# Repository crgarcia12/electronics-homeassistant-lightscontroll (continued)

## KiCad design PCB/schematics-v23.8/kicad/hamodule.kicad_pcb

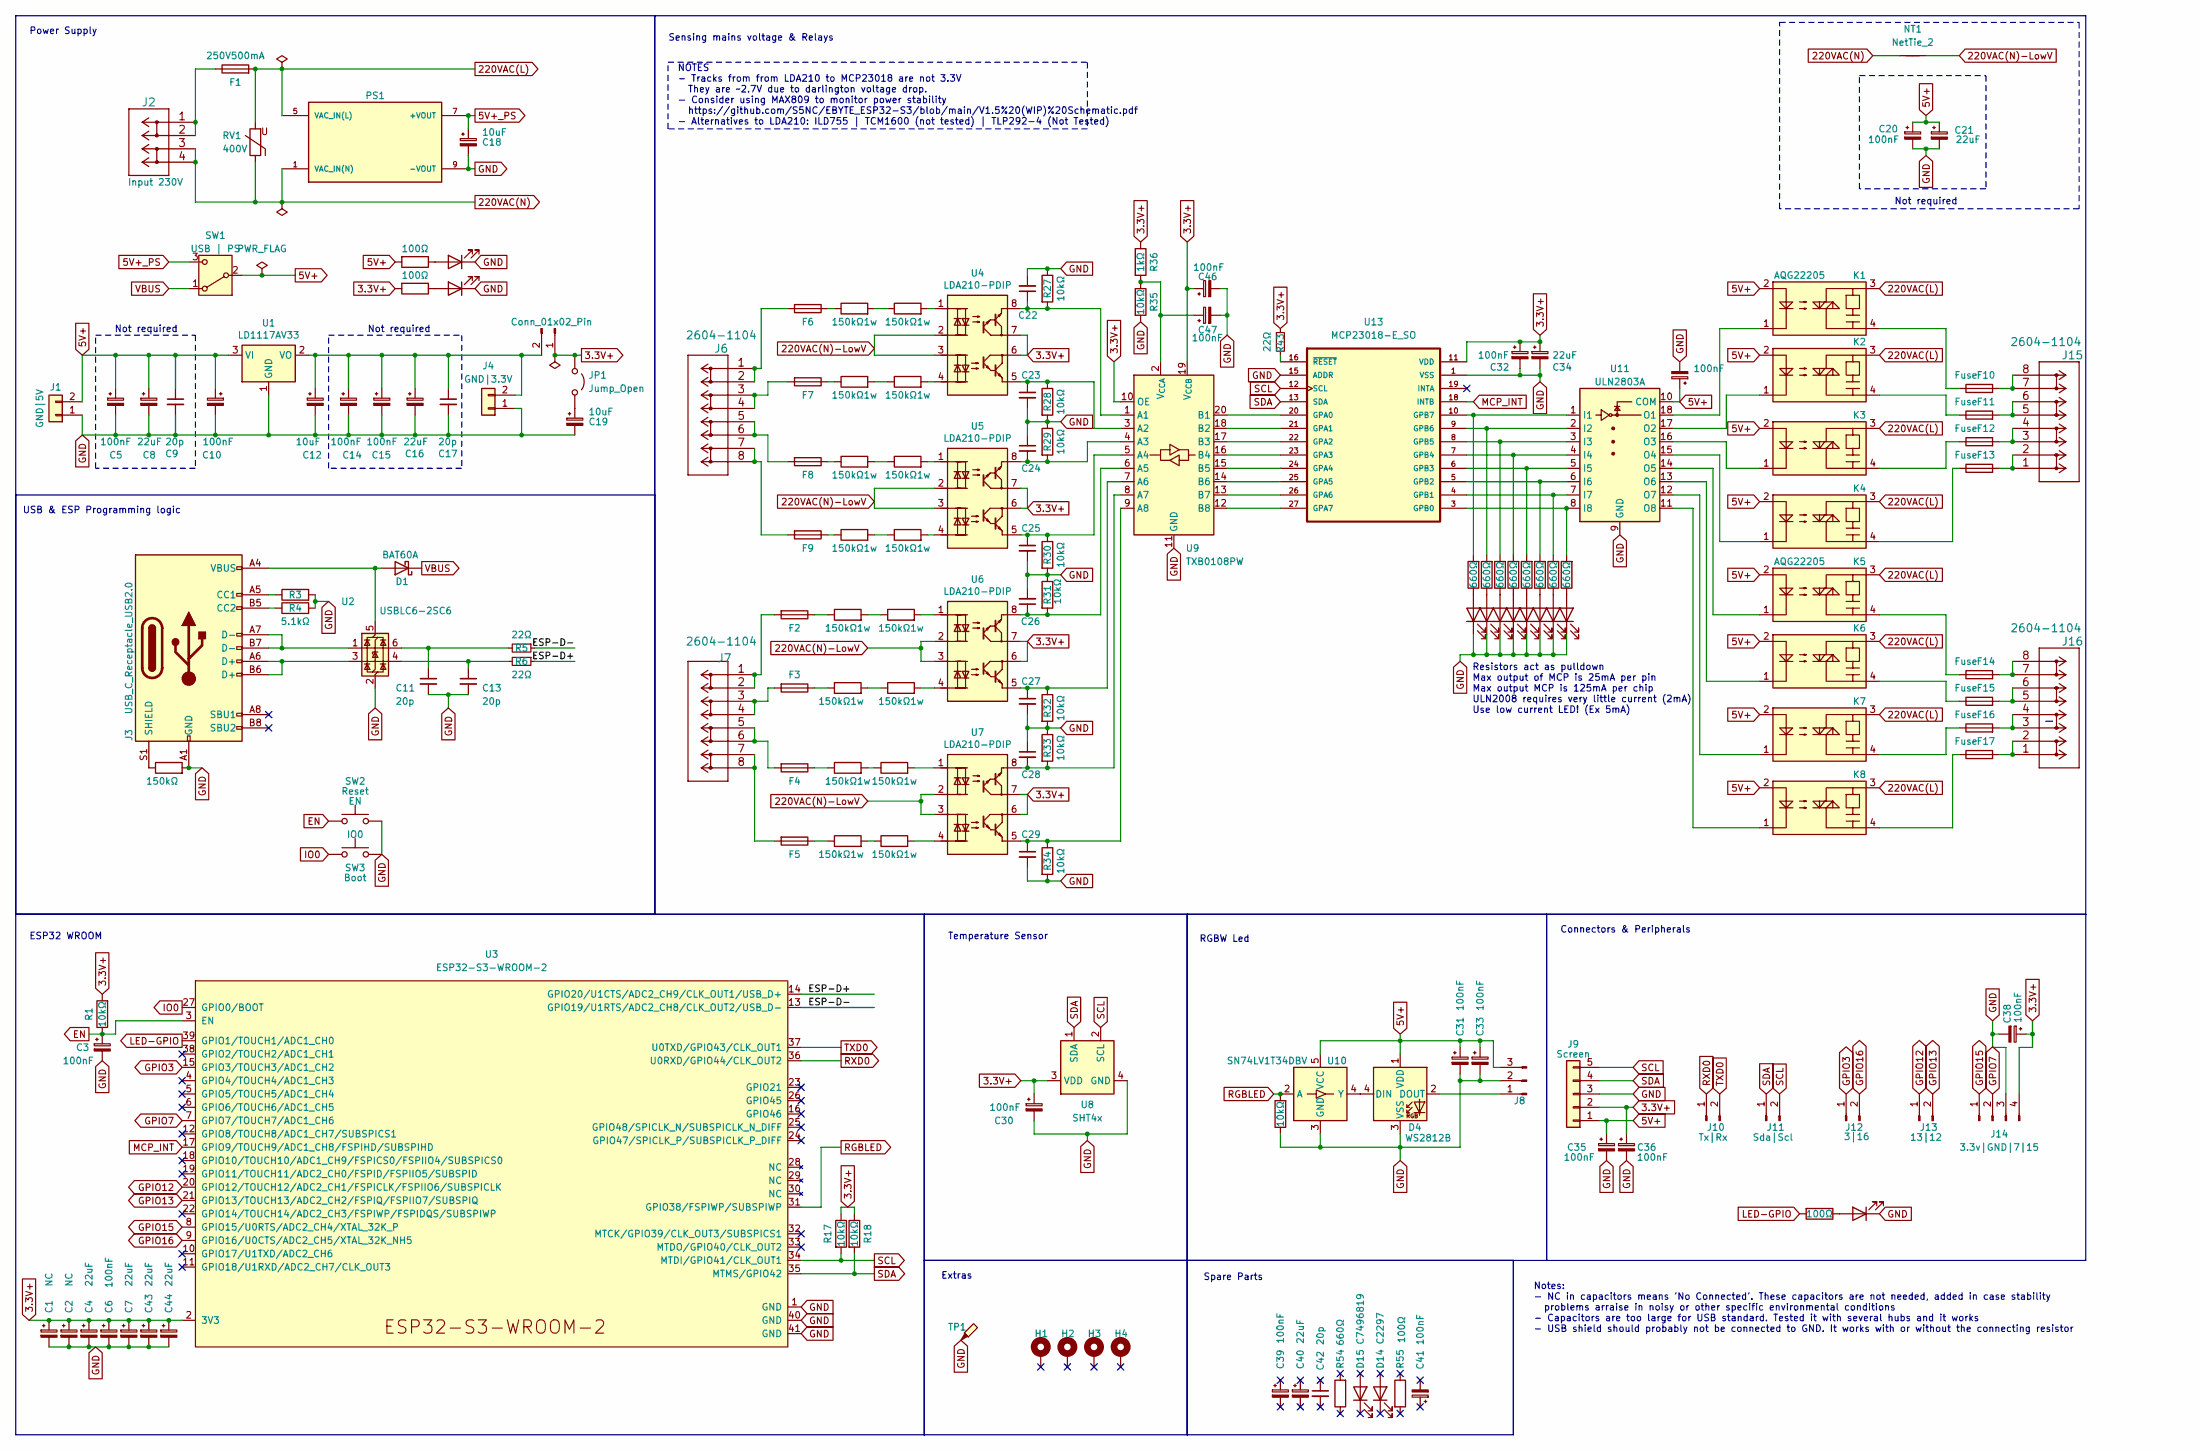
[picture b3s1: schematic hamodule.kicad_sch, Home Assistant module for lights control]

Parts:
C1, C2: NC; C_1206_3216Metric_Pad1.33x1.80mm_HandSolder
C3, C6, C30, C31, C33, C39, C46, C47: 100nF; C_0603_1608Metric_Pad1.08x0.95mm_HandSolder; JLCPCB C14663
C4, C22, C23, C24, C25, C26, C27, C28, C29, C34, C40: 22uF; C_0603_1608Metric_Pad1.08x0.95mm_HandSolder; JLCPCB C59461
C5, C10, C14, C15, C20, C32, C35, C36, C37, C38, C41: 100nF; C_0805_2012Metric_Pad1.18x1.45mm_HandSolder; JLCPCB C49678
C7, C8, C16, C21: 22uF; C_0805_2012Metric_Pad1.18x1.45mm_HandSolder; JLCPCB C45783
C9, C11, C13, C17, C42: 20p; C_0603_1608Metric_Pad1.08x0.95mm_HandSolder; LCSC C1648
C12, C18, C19: 10uF; CP_Radial_D6.3mm_P2.50mm
C43, C44: 22uF; C_0402_1005Metric; LCSC \
D1: BAT60A; D_SOD-323; JLCPCB C124187
D2: 5V; LED_0805_2012Metric_Pad1.15x1.40mm_HandSolder; JLCPCB C2297
D3: 3.3V; LED_0805_2012Metric_Pad1.15x1.40mm_HandSolder; JLCPCB C2297
D4: WS2812B; LED_WS2812B_PLCC4_5.0x5.0mm_P3.2mm; JLCPCB C5446705
D5, D6, D7, D8, D9, D10, D11, D12: LED; LED_0603_1608Metric; JLCPCB C7496819
D13: LED; LED_0805_2012Metric_Pad1.15x1.40mm_HandSolder; JLCPCB C2297
D14: C2297; LED_0805_2012Metric_Pad1.15x1.40mm_HandSolder; JLCPCB C2297
D15: C7496819; LED_0603_1608Metric; JLCPCB C7496819
F1: 250V500mA; Fuseholder_TR5_Littelfuse_No560_No460
F2, F3, F4, F5, F6, F7, F8, F9, F10, F11, F12, F13, F14, F15, F16, F17: Fuse; FUSE_RST-1-BULK
H1, H2, H3, H4: MountingHole_Pad; MountingHole_3.2mm_M3_ISO14580_Pad
J1: GND|5V; JST_XH_B2B-XH-A_1x02_P2.50mm_Vertical
J2: 2604-1102; big_pads_2604-1102
J3: USB_C_Receptacle_USB2.0; USB_C_Receptacle_HRO_TYPE-C-31-M-12; JLCPCB C2927038
J4: GND|3.3V; JST_XH_B2B-XH-A_1x02_P2.50mm_Vertical
J5: Conn_01x02_Pin; PinHeader_1x02_P2.54mm_Vertical; JLCPCB C492401
J6, J7, J15, J16: 2604-1104; big_pads_2604-1104
J8: 5v|GND|Do; PinHeader_1x03_P2.54mm_Vertical; JLCPCB C49257
J9: Screen; JST_XH_B5B-XH-A_1x05_P2.50mm_Vertical
J10: Tx|Rx; PinHeader_1x02_P2.54mm_Vertical; JLCPCB C492401
J11: Sda|Scl; PinHeader_1x02_P2.54mm_Vertical; JLCPCB C492401
J12: 3|16; PinHeader_1x02_P2.54mm_Vertical; JLCPCB C492401
J13: 13|12; PinHeader_1x02_P2.54mm_Vertical; JLCPCB C492401
J14: 3.3v|GND|7|15; PinHeader_1x04_P2.54mm_Vertical
JP1: Jump_Open; SolderJumper-2_P1.3mm_Bridged2Bar_RoundedPad1.0x1.5mm
K1, K2, K3, K4, K5, K6, K7, K8: AQG22205; AQG12205; Manufacturer_Part_Number AQG12205; Mouser Part Number 769-AQG12205
NT1: NetTie_2; NetTie-2_SMD_Pad2.0mm
PS1: RAC05-05SK/277; 277; PARTREV N/A
R1, R17, R18, R27, R28, R29, R30, R31, R32, R33, R34, R35, R44: 10kΩ; R_0603_1608Metric_Pad0.98x0.95mm_HandSolder; JLCPCB C25804
R2: 150kΩ; R_0805_2012Metric_Pad1.20x1.40mm_HandSolder; JLCPCB C17470
R3, R4: 5.1kΩ; R_0603_1608Metric_Pad0.98x0.95mm_HandSolder; JLCPCB C23186
R5, R6, R43: 22Ω; R_0603_1608Metric; LCSC C23345
R7, R8, R53, R55: 100Ω; R_0805_2012Metric_Pad1.20x1.40mm_HandSolder; JLCPCB C17408
R9, R10, R11, R12, R13, R14, R15, R16, R19, R20, R21, R22, R23, R24, R25, R26: 150kΩ1w; R_2512_6332Metric_Pad1.40x3.35mm_HandSolder; JLCPCB C25719
R36: 1kΩ; R_0603_1608Metric_Pad0.98x0.95mm_HandSolder
R45, R46, R47, R48, R49, R50, R51, R52, R54: 660Ω; R_0603_1608Metric_Pad0.98x0.95mm_HandSolder; JLCPCB C23193
RV1: 400V; RV_Disc_D12mm_W4.2mm_P7.5mm
SW1: USB | PS; PinHeader_1x03_P2.54mm_Vertical
SW2: Reset; SW_SPST_SKQG_WithStem; JLCPCB C318884
SW3: Boot; SW_SPST_SKQG_WithStem; JLCPCB C318884
TP1: GND; TestPoint_THTPad_1.0x1.0mm_Drill0.5mm
U1: LD1117AV33; TO-220-3_Vertical
U2: USBLC6-2SC6; SOT-23-6; JLCPCB C2827654
U3: ESP32-S3-WROOM-2; JLCPCB C2913202
U4, U5, U6, U7: LDA210-PDIP; DIP-8_W7.62mm_Socket_LongPads
U8: SHT4x; Sensirion_DFN-4_1.5x1.5mm_P0.8mm_SHT4x_NoCentralPad; JLCPCB C2909890
U9: TXB0108PW; TSSOP-20_4.4x6.5mm_P0.65mm
U10: SN74LV1T34DBV; SOT-23-5; JLCPCB C100024
U11: ULN2803A; SOP-18_7x12.5mm_P1.27mm; JLCPCB C845537
U13: MCP23018-E_SO; SOIC-28W_7.5x17.9mm_P1.27mm; JLCPCB C646064

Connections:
3.3V+: C1.1, C2.1, C4.1, C6.1, C7.1, C30.1, C32.1, C34.1, C36.1, C38.1, C43.1, C44.1, C46.1, J5.1, J9.2, J14.4, JP1.1 (A), R1.2, R8.2, R17.1, R18.1, R36.1, R43.1, U3.2 (3V3), U4.6, U4.7, U5.6, U5.7, U6.6, U6.7, U7.6, U7.7, U8.3 (VDD), U9.10 (OE), U9.19 (V_{CCB}), U13.11 (VDD)
5V+: C5.1, C8.1, C9.1, C10.1, C20.1, C21.1, C31.1, C33.1, C35.1, C37.1, D4.1 (VDD), J1.2, J8.3, J9.1, K1.2, K2.2, K3.2, K4.2, K5.2, K6.2, K7.2, K8.2, R7.2, SW1.2 (B), U1.3 (VI), U10.5 (VCC), U11.10 (COM)
5V+_PS: C18.1, PS1.7 (+VOUT), SW1.3 (C)
220VAC(L): F1.2, K1.3, K2.3, K3.3, K4.3, K5.3, K6.3, K7.3, K8.3, PS1.5 (VAC_IN(L)), RV1.2
220VAC(N): J2.3, J2.4, NT1.1, PS1.1 (VAC_IN(N)), RV1.1
220VAC(N)-LowV: NT1.2, U4.2, U4.3, U5.2, U5.3, U6.2, U6.3, U7.2, U7.3
/ESP-D+: R6.1, U3.14 (GPIO20/U1CTS/ADC2_CH9/CLK_OUT1/USB_D+)
/ESP-D-: R5.1, U3.13 (GPIO19/U1RTS/ADC2_CH8/CLK_OUT2/USB_D-)
EN: C3.1, R1.1, SW2.1, U3.3 (EN)
GND: C1.2, C2.2, C3.2, C4.2, C5.2, C6.2, C7.2, C8.2, C9.2, C10.2, C11.2, C12.2, C13.2, C14.2, C15.2, C16.2, C17.2, C18.2, C19.2, C20.2, C21.2, C22.2, C23.2, C24.1, C25.2, C26.2, C27.2, C28.1, C29.2, C30.2, C31.2, C32.2, C33.2, C34.2, C35.2, C36.2, C37.2, C38.2, C43.2, C44.2, C46.2, C47.2, D2.1 (K), D3.1 (K), D4.3 (VSS), D5.1 (K), D6.1 (K), D7.1 (K), D8.1 (K), D9.1 (K), D10.1 (K), D11.1 (K), D12.1 (K), D13.1 (K), J1.1, J3.A1 (GND), J3.A12 (GND), J3.B1 (GND), J3.B12 (GND), J4.1, J8.2, J9.3, J14.3, PS1.9 (-VOUT), R2.2, R3.2, R4.2, R27.1, R28.2, R29.1, R30.2, R31.1, R32.2, R33.1, R34.2, R35.2, R44.1, SW2.2, SW3.2, TP1.1, U1.1 (GND), U2.2 (GND), U3.1 (GND), U3.40 (GND), U3.41 (GND), U8.4 (GND), U9.11 (GND), U10.3 (GND), U11.9 (GND), U13.1 (VSS), U13.15 (ADDR)
GPIO3: J12.1, U3.15 (GPIO3/TOUCH3/ADC1_CH2)
GPIO7: J14.2, U3.7 (GPIO7/TOUCH7/ADC1_CH6)
GPIO12: J13.1, U3.20 (GPIO12/TOUCH12/ADC2_CH1/FSPICLK/FSPIIO6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)
GPIO13: J13.2, U3.21 (GPIO13/TOUCH13/ADC2_CH2/FSPIQ/FSPIIO7/S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)
GPIO15: J14.1, U3.8 (GPIO15/U0RTS/ADC2_CH4/XTAL_32K_P)
GPIO16: J12.2, U3.9 (GPIO16/U0CTS/ADC2_CH5/XTAL_32K_NH5)
IO0: SW3.1, U3.27 (GPIO0/BOOT)
LED-GPIO: R53.2, U3.39 (GPIO1/TOUCH1/ADC1_CH0)
MCP_INT: U3.17 (GPIO9/TOUCH9/ADC1_CH8/FSPIHD/SUBSPIHD), U13.18 (INTB)
unnamed: C11.1, R5.2, U2.6 (I/O1)
unnamed: C13.1, R6.2, U2.4 (I/O2)
unnamed: D1.2 (A), J3.A4 (VBUS), J3.A9 (VBUS), J3.B4 (VBUS), J3.B9 (VBUS), U2.5 (VBUS)
unnamed: D2.2 (A), R7.1
unnamed: D3.2 (A), R8.1
unnamed: D4.4 (DIN), U10.4 (Y)
unnamed: D4.2 (DOUT), J8.1
unnamed: D5.2 (A), R45.1
unnamed: D6.2 (A), R46.1
unnamed: D7.2 (A), R47.1
unnamed: D8.2 (A), R48.1
unnamed: D9.2 (A), R49.1
unnamed: D10.2 (A), R50.1
unnamed: D11.2 (A), R51.1
unnamed: D12.2 (A), R52.1
unnamed: D13.2 (A), R53.1
unnamed: F1.1, J2.1, J2.2
unnamed: F2.1, R9.1
unnamed: F2.2, J7.1, J7.2
unnamed: F3.1, R10.1
unnamed: F3.2, J7.3, J7.4
unnamed: F4.1, R11.1
unnamed: F4.2, J7.5, J7.6
unnamed: F5.1, R12.1
unnamed: F5.2, J7.7, J7.8
unnamed: F6.1, R13.1
unnamed: F6.2, J6.1, J6.2
unnamed: F7.1, R14.1
unnamed: F7.2, J6.3, J6.4
unnamed: F8.1, R15.1
unnamed: F8.2, J6.5, J6.6
unnamed: F9.1, R16.1
unnamed: F9.2, J6.7, J6.8
unnamed: F10.1, K1.4
unnamed: F10.2, J15.7, J15.8
unnamed: F11.1, K2.4
unnamed: F11.2, J15.5, J15.6
unnamed: F12.1, K3.4
unnamed: F12.2, J15.3, J15.4
unnamed: F13.1, K4.4
unnamed: F13.2, J15.1, J15.2
unnamed: F14.1, K5.4
unnamed: F14.2, J16.7, J16.8
unnamed: F15.1, K6.4
unnamed: F15.2, J16.5, J16.6
unnamed: F16.1, K7.4
unnamed: F16.2, J16.3, J16.4
unnamed: F17.1, K8.4
unnamed: F17.2, J16.1, J16.2
unnamed: J3.A5 (CC1), R3.1
unnamed: J3.B5 (CC2), R4.1
unnamed: J3.A6 (D+), J3.B6 (D+), U2.3 (I/O2)
unnamed: J3.A7 (D-), J3.B7 (D-), U2.1 (I/O1)
unnamed: J3.S1 (SHIELD), R2.1
unnamed: C12.1, C14.1, C15.1, C16.1, C17.1, J4.2, J5.2, U1.2 (VO)
unnamed: C19.1, JP1.2 (B)
unnamed: R10.2, R22.1
unnamed: R11.2, R19.1
unnamed: R12.2, R20.1
unnamed: R13.2, R23.1
unnamed: R14.2, R24.1
unnamed: R15.2, R25.1
unnamed: R16.2, R26.1
unnamed: R19.2, U7.1
unnamed: R20.2, U7.4
unnamed: R9.2, R21.1
unnamed: R21.2, U6.1
unnamed: R22.2, U6.4
unnamed: R23.2, U4.1
unnamed: R24.2, U4.4
unnamed: R25.2, U5.1
unnamed: R26.2, U5.4
unnamed: C22.1, R27.2, U4.8, U9.1 (A1)
unnamed: C23.1, R28.1, U4.5, U9.3 (A2)
unnamed: C24.2, R29.2, U5.8, U9.4 (A3)
unnamed: C25.1, R30.1, U5.5, U9.5 (A4)
unnamed: C26.1, R31.2, U6.8, U9.6 (A5)
unnamed: C27.1, R32.1, U6.5, U9.7 (A6)
unnamed: C28.2, R33.2, U7.8, U9.8 (A7)
unnamed: C29.1, R34.1, U7.5, U9.9 (A8)
unnamed: C47.1, R35.1, R36.2, U9.2 (V_{CCA})
unnamed: R45.2, U11.1 (I1), U13.10 (GPB7)
unnamed: R46.2, U11.2 (I2), U13.9 (GPB6)
unnamed: R47.2, U11.3 (I3), U13.8 (GPB5)
unnamed: R48.2, U11.4 (I4), U13.7 (GPB4)
unnamed: R49.2, U11.5 (I5), U13.6 (GPB3)
unnamed: R50.2, U11.6 (I6), U13.5 (GPB2)
unnamed: R51.2, U11.7 (I7), U13.4 (GPB1)
unnamed: R52.2, U11.8 (I8), U13.3 (GPB0)
unnamed: K1.1, U11.18 (O1)
unnamed: K2.1, U11.17 (O2)
unnamed: K3.1, U11.16 (O3)
unnamed: K4.1, U11.15 (O4)
unnamed: K5.1, U11.14 (O5)
unnamed: K6.1, U11.13 (O6)
unnamed: K7.1, U11.12 (O7)
unnamed: K8.1, U11.11 (O8)
unnamed: U9.20 (B1), U13.20 (GPA0)
unnamed: U9.18 (B2), U13.21 (GPA1)
unnamed: U9.17 (B3), U13.22 (GPA2)
unnamed: U9.16 (B4), U13.23 (GPA3)
unnamed: U9.15 (B5), U13.24 (GPA4)
unnamed: U9.14 (B6), U13.25 (GPA5)
unnamed: U9.13 (B7), U13.26 (GPA6)
unnamed: U9.12 (B8), U13.27 (GPA7)
unnamed: R43.2, U13.16 (~RESET)
RGBLED: R44.2, U3.31 (GPIO38/FSPIWP/SUBSPIWP), U10.2 (A)
RXD0: J10.1, U3.36 (U0RXD/GPIO44/CLK_OUT2)
SCL: J9.5, J11.2, R17.2, U3.34 (MTDI/GPIO41/CLK_OUT1), U8.2 (SCL), U13.12 (SCL)
SDA: J9.4, J11.1, R18.2, U3.35 (MTMS/GPIO42), U8.1 (SDA), U13.13 (SDA)
TXD0: J10.2, U3.37 (U0TXD/GPIO43/CLK_OUT1)
VBUS: D1.1 (K), SW1.1 (A)

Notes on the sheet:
USB & ESP Programming logic
NOTES - Tracks from from LDA210 to MCP23018 are not 3.3V They are ~2.7V due to darlington voltage drop. - Consider using MAX809 to monitor power stability https://github.com/S5NC/EBYTE_ESP32-S3/blob/main/V1.5%20(WIP)%20Schematic.pdf - Alternatives to LDA210: ILD755 | TCM1600 (not tested) | TLP292-4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
Spare Parts
Temperature Sensor
Power Supply
Extras
Not required
Resistors act as pulldown Max output of MCP is 25mA per pin Max output MCP is 125mA per chip ULN2008 requires very little current (2mA) Use low current LED! (Ex 5mA)
Connectors & Peripherals
ESP32 WROOM
RGBW Led
Notes: - NC in capacitors means 'No Connected'. These capacitors are not needed, added in case stability problems arraise in noisy or other specific environmental conditions - Capacitors are too large for USB standard. Tested it with several hubs and it works - USB shield should probably not be con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
Sensing mains voltage & Relays

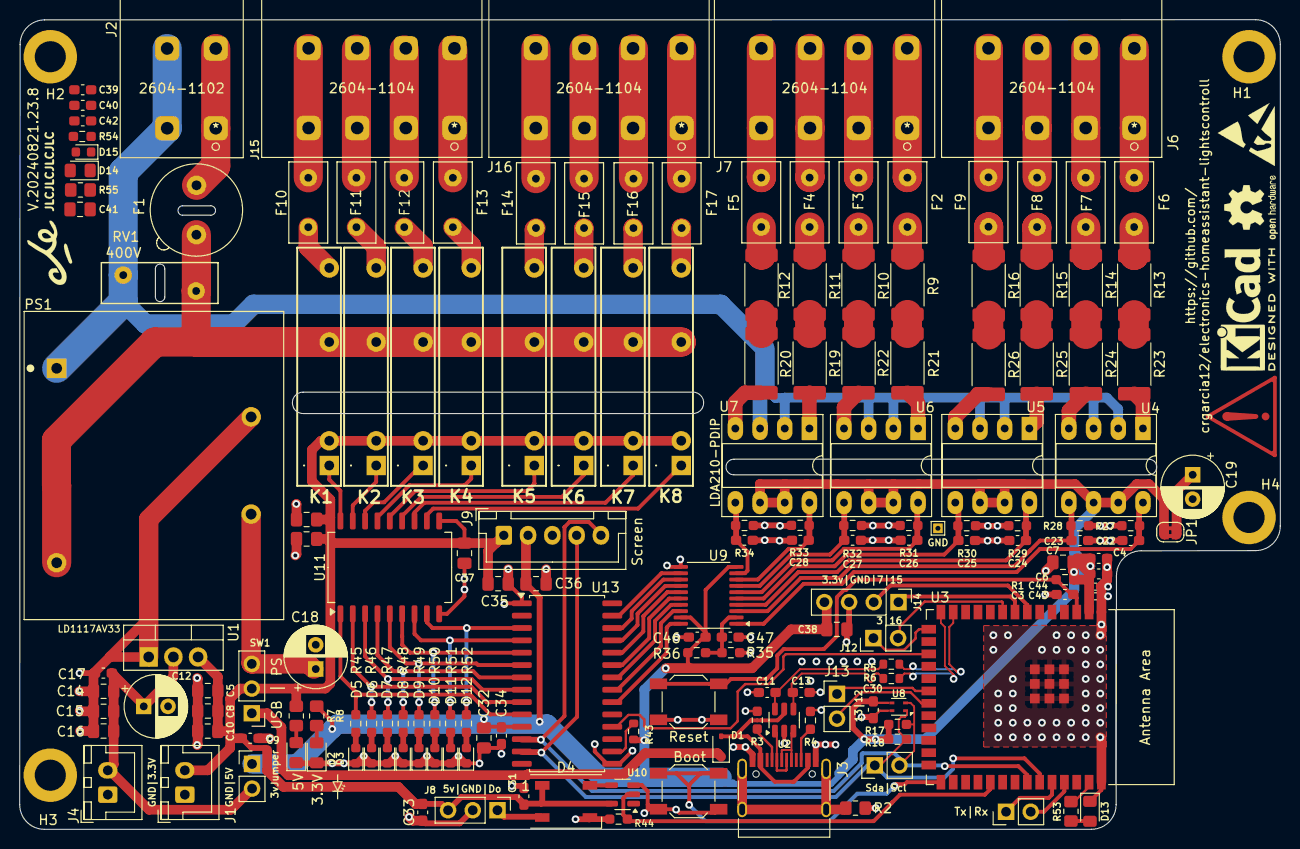
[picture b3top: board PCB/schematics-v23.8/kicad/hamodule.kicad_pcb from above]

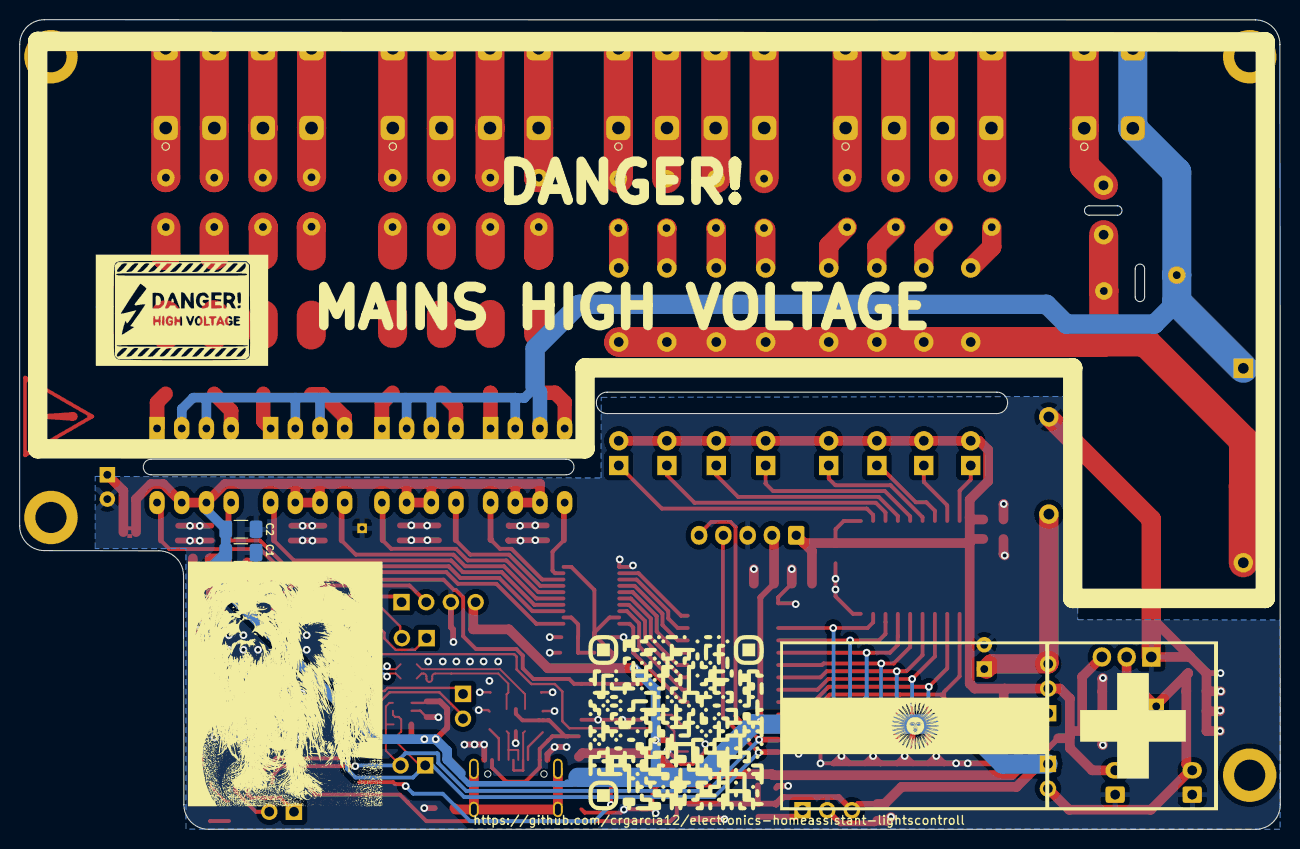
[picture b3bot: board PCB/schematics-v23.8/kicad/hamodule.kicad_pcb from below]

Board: 4 copper layers, 129.7 x 83.3 mm, 185 parts (7 on the bottom side), 131 nets.

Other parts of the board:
G1: LOGO; depsi
G2: LOGO; flags
G3: LOGO; qr_code_m
G4: LOGO; led_6000dpi
G5: LOGO; danger1_negative
G6: KiCad-Logo2_5mm_SilkScreen
G7: OSHW-Logo2_7.3x6mm_SilkScreen
G8: ESD-Logo_6.6x6mm_SilkScreen
G9: Symbol_Attention_Triangle_8x7mm_Copper
G10: LOGO; che

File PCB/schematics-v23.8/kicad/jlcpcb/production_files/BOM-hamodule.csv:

Comment,Designator,Footprint,LCSC
SN74LV1T34DBV,U10,SOT-23-5,C100024
BAT60A,D1,D_SOD-323,C124187
100nF,"C3,C30,C31,C33,C39,C6",C_0603_1608Metric_Pad1.08x0.95mm_HandSolder,C14663
20p,"C11,C13,C17,C42,C9",C_0603_1608Metric_Pad1.08x0.95mm_HandSolder,C1648
100Ω,"R53,R55,R7,R8",R_0805_2012Metric_Pad1.20x1.40mm_HandSolder,C17408
150kΩ,R2,R_0805_2012Metric_Pad1.20x1.40mm_HandSolder,C17470
LED,"D13,D14,D2,D3",LED_0805_2012Metric_Pad1.15x1.40mm_HandSolder,C2297
33Ω,"R35,R36,R37,R38,R39,R40,R41,R42",R_0603_1608Metric_Pad0.98x0.95mm_HandSolder,C23140
5.1kΩ,"R3,R4",R_0603_1608Metric_Pad0.98x0.95mm_HandSolder,C23186
660Ω,"R45,R46,R47,R48,R49,R50,R51,R52,R54",R_0603_1608Metric_Pad0.98x0.95mm_HandSolder,C23193
22Ω,"R43,R5,R6",R_0603_1608Metric,C23345
150kΩ1w,"R10,R11,R12,R13,R14,R15,R16,R19,R20,R21,R22,R23,R24,R25,R26,R9",R_2512_6332Metric_Pad1.40x3.35mm_HandSolder,C25719
10kΩ,"R1,R17,R18,R27,R28,R29,R30,R31,R32,R33,R34,R44",R_0603_1608Metric_Pad0.98x0.95mm_HandSolder,C25804
USBLC6-2SC6,U2,SOT-23-6,C2827654
SHT4x,U8,Sensirion_DFN-4_1.5x1.5mm_P0.8mm_SHT4x_NoCentralPad,C2909890
ESP32-S3-WROOM-2,U3,ESP32-S3-WROOM-2,C2913202
USB_C_Receptacle_USB2.0,J3,USB_C_Receptacle_HRO_TYPE-C-31-M-12,C2927038
Reset,"SW2,SW3",SW_SPST_SKQG_WithStem,C318884
22uF,"C16,C21,C7,C8",C_0805_2012Metric_Pad1.18x1.45mm_HandSolder,C45783
Tx|Rx,"J10,J11,J12,J13,J5",PinHeader_1x02_P2.54mm_Vertical,C492401
5v|GND|Do,J8,PinHeader_1x03_P2.54mm_Vertical,C49257
100nF,"C10,C14,C15,C20,C32,C35,C36,C37,C38,C41,C5",C_0805_2012Metric_Pad1.18x1.45mm_HandSolder,C49678
WS2812B,D4,LED_WS2812B_PLCC4_5.0x5.0mm_P3.2mm,C5446705
22uF,"C22,C23,C24,C25,C26,C27,C28,C29,C34,C4,C40",C_0603_1608Metric_Pad1.08x0.95mm_HandSolder,C59461
MCP23018-E_SO,U13,SOIC-28W_7.5x17.9mm_P1.27mm,C646064
LED,"D10,D11,D12,D15,D5,D6,D7,D8,D9",LED_0603_1608Metric,C7496819
ULN2803A,U11,SOP-18_7x12.5mm_P1.27mm,C845537
